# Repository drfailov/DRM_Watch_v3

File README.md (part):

<!-- For new line: \ -->
<!-- Picture:   -->
<!-- New Line: "  <br>"  -->

# Про проект DRM Watch 3

**DRM Watch 3** - це мій саморобний наручний годинник, в основі якого лежить дисплей Sharp Memory LCD, ESP32-S2 і бажання носити це на руці:)  <br>
Це **НЕ "Smart годинник"**! Цей пристрій по своїй функціональності близький до звичайного електронного годинника, з кількома додатковими можливостями, і їх можна додавати, перепрограмовувати годинник під себе.  <br>
Наразі в прошивці є всі можливості, що притаманні типовому годиннику і що дозволяє повноцінно використовувати його на щоденній основі.  <br>
В цьому репозиторії можна знайти інфу і інструкції **щоб зібрати собі такий годинник**.  <br>
  <br>
Це у мене таке хобі:) Я в кінці 2023 поліз вивчати проектування плат, після появи 3д принтера в 2022 поліз вивчати 3д моделювання, а за освітою програміст.  От власне це все і зібралось воєдино в цьому проекті) Робив це все з нуля. А яка б класна з цього була дипломна робота)))  <br>
  <br>
Посилання що наведено в цьому тексті є актуальними станом на **2024-04**. Якщо якісь товари будуть вже не актуальні, то шукайте за фотками))  <br>
  <br>
Стаття на Instructables:  <br>
https://www.instructables.com/DIY-ESP32-Wearable-DRM-Watch-3/    <br>
	  <br>

## Фото
<!--p align="center">

</p-->

<!--p align="center">

</p-->

## Особливості годинника
- Зроблено в Україні;
- Стабільно працює і підходить для щоденного користування;
- Дисплей завжди показує час;
- Інтерфейс двома мовами: Українська та Англійська.
- В годиннику є вбудована "флешка" на 1.2МБ, в яку можна закинути файли
- Годинник може відкрити монохромний BMP, Wav файли, текстовий TXT документи
- Є дуже тускла але дуже приємна нічна підсвітка дисплея;
- Є ліхтарик, білий яскравий та червоний нічний;
- Акумулятора вистачає на понад 14днів, є індикатор заряду;
- Зручні меню, звідки можна отримати доступ до всіх функцій;
- Наявність Wi-Fi, можна зберегти до 8 мереж в пам'яті;
- Можливість синхронізації часу по Wi-Fi;
- Багато мелодій. Їх можна або просто слухати або встановити на будильник.
- Імітація звуку мявчання кошенят;
- Кілька циферблатів, які можна налаштувати;
- На циферблати можна додати календар, стрілочний годинник, дату, та цікавий фон
- Секундомір, працює в фоні;
- Будильники, до 6шт з назвами;
- Вічний календар (або я ще не догортав до кінця);
- Повнекранні клітинні автомати та анімації (Життя, Мураха, Вогонь, Шум, Лава, Мураха, Точки)
- Зарядка по USB, в тому числі від TypeC-TypeC;
- Можна оновлювати прошивку по USB, не розбираючи годинник.
- Компоненти для збірки легко дістати;
- Корпус підходить для стандартних 22мм ремінців;
- Зручно і просто прошивати. Можна написати свою прошивку.
- Якщо під час експериментів з прошивками годинник завис, в корпусі передбачено отвір щоб голкою його перезавантажити.
- Водонепроникність до 0 метрів:) (можна трохи покращити якщо при збірці обробити плату лаком а корпус збирати з клеєм.)
- Годинник можна використовувати як поле для експериментів з ESP32-S2: акумулятор, 3 кнопки, пищалка, дисплей, 3 світлодіоди;
- UART лог: інструмент для розробників, виводить на екран всі байти що надходять по UART.
- Екран "Про годинник" містить інформацію про розробника та версію прошивки.

## Застереження під час користування:

- Годинник **не можна мочити**. Захист від води тут майже відсутній і це призведе до поломки годинника. Від дрібного дощу або поту йому нічого не буде, а от залити при митті рук - може бути проблемою.
- Годинник **слабко захищений від ударів**. Дисплей не захищений, тонкі рамки, тонкий корпус, годинник спроектований без великого запасу механічної міцності, так він  ще й досить габаритний. Тому вдарити його легко, і це скоріше за все призведе до розбитого дисплея. Протягом моїх місяців експлуатації проблем з пошкодженням годинника не було, але я користувався досить обережно.
- Годинник варто **оберігати від впливу статики**. Є невеликий шанс вбити годинник якщо швидко змімати з себе светр) Тому або знімайте светр повільно, або зніміть перед цим годинник, або використовуйте светр який не електризується. Особливо ризикований момент - постановка на зарядку, тут може проскочити прямо через контроллер. Раджу перед тим як вставити кабель зарядки, доторкнутись до металевої частини корпусу зарядного пристрою - так ви розрядитесь через корпус, а не через годинник і все буде ок.

## Відео огляди годинника:
Тут я зібрав наявні відео годинника.

### Короткий огляд станом на FW v2.03
  <br>
https://www.youtube.com/watch?v=3oIwZVaCEvY

### Повний огляд годинника станом на FW v3.22
  <br>
https://youtu.be/EeJpstsf5wk?si=9BsKVnumjvJCgt0X

## Короткий відео огляд мелодій станом на FW v2.03
  <br>
https://www.youtube.com/watch?v=Ylm3CU0DTDE

### Мій акаунт тікток, де відео багато
  <br>
https://www.tiktok.com/@drfailov

# Опис меню, функцій та екранів

## Основний екран, циферблат
<p align="center"> 

<!--img src="Photos/photo_2_2024-06-02_22-49-14.jpg" height=200"/> 

</p>

Тут відображаєтья час. Це основний екран годинника, на нього переходят більшість екранів по таймеру бездіяльності. На цьому екрані годинник заходить в сон і спить, просинаючись раз в хвилину щоб намалювати час.     <br>
Вміст циферблату можна налаштувати під себе, тому тут так багато різних його фоток        <br>
**Кнопка вгору** (коротке натиснення) - Відкрити секундомір.      <br>
**Кнопка вгору** (довге натиснення) - Відкрити таймер.      <br>
**Середня кнопка** (коротке натиснення) - Увімкнути ліхтарик.      <br>
**Середня кнопка** (довге натиснення) - вимкнути годинник.      <br>
**Кнопка вниз** - відкрити меню програм.      <br>

## Програми

<p align="center"> 
 
<!--img src="Photos/photo_3_2024-06-02_22-49-14.jpg" height=300"/--> 
</p>

Звідси можна запустити функції які не є налаштуваннями. Будильники, секундоміри, ігри, розваги, тощо.     <br>
З цього екрану годинник автоматично перейде на основний екран через кілька хвилин бездіяльності.    <br>
**Кнопками вгору та вниз** - обрати пункт меню.     <br>
**Центральна кнопка** - активує обраний пункт меню.      <br>

## Програми -> Будильник

Будильник запускає відтворення заданої мелодії в заданий час дня.     <br>
З цього екрану годинник автоматично перейде на основний екран через кілька хвилин бездіяльності.    <br>
Можна налаштувати кілька будильників. До кожного можна задати час, назву та мелодію. Будильник спрацює якщо годинник заряджений і якщо годинник звісно знає поточний час. Спрацює також якщо в момент спрацювання ви знаходитесь в меню а не на циферблаті, а також спрацює якщо годинник вимкнено (але він при цьому заряджений).     <br>
**Кнопками вгору та вниз** - обрати пункт меню.      <br>
**Центральна кнопка** активує обраний пункт меню.      <br>
Коли пункт меню активований, **кнопки вниз та вгору міняють значення пункту**.     <br>
Під час будильника гратиме обрана мелодія і відображатиметься назва будильника та час на який будильник було встановлено. Під час спрацювання будильника його можна закрити (вимкнути на поточний раз), або вікласти на 10 або 5 хвилин (за умови якщо в цей момент не запущено таймер). Після спрацювання будильника він спрацює знову наступного дня. 

## Програми -> Календар

<p align="center"> 
 
<!--img src="Photos/photo_14_2024-06-02_22-49-14.jpg" height=300"/--> 
</p>

Показує календар на місяць.     <br>
З цього екрану годинник автоматично перейде на основний екран через кілька хвилин бездіяльності.    <br>
**Кнопками вгору та вниз** - змінити поточний місяць.     <br>
**Центральна кнопка** - вийти.     <br>

## Налаштування

## Налаштування -> Дисплей

### Інверсія

### Мова

### Калібрування акумулятора 

Кожен годинник - унікальний, тому кожен показує заряд по своєму.      <br>
Щоб компенсувати цю неточність, я додав алгоритм який це виправляє, але для цього йому потрібно знати свою криву розряду. Щоб провести калібрування:      <br>
- повністю зарядити годинник 
- зняти з зарядки і пройти в налаштування -> дисплей ->калібрування акумулятора
- натиснути там початок калібровки.
- лишити годинник увімкненим на кілька годин поки він не вимкнеться.
Коли годинник вимкнеться, його можна поставити на зарядку і після цього він буде готовий до роботи з новою калібровкою     

## Програми -> Файли

Важливо!!! Не зберігайте на годиннику цінну інформацію яка не має копії! У мене кілька разів "ламалась" файлова система і файли втрачались. 
Закономірностей цього явища поки не виявив, але я б не довіряв годиннику нічого цінного!

Формати файлів які може відкрити годинник:
- BMP монохромний. Такі файли можна сформувати з допомогою Microsoft Paint.
- DWM мелодії. Такі файли можна сформувати з допомогою програми в папці `Software\MIDI-to-Arduino-main`.
- WAV PCM 8bit аудіо. Такі файли можна сформувати з допомогою Audacity.
- TXT текстові файли в UTF8 кодуванні. Такі файли можна сформувати з допомогою Notepad++.

## Програми -> Менеджер пам'яті

**Підключити до USB** - імітує підключену флешку.
**Показати карту розділів** - Відображає як поділена пам'ять ESP32.

## Програми -> Мелодії

Меню зі списком мелодій. Можна переглянути назви та увімкнути мелодію. Їх там багато.     <br>
Я постійно додаю нові мелодії, зокрема з мемів. Додати свої мелодії також можливо, дивіться розділ як зібрати прошивку а потім як додати мелодію.     <br>
З цього екрану годинник автоматично перейде на основний екран через кілька хвилин бездіяльності.    <br>
**Кнопками вгору та вниз** - обрати мелодію.     <br>
**Центральна кнопка** - відкрити і відтворити мелодію.   <br>

## Програми -> Мелодії -> Плеєр

Коли грає мелодія. Цей екран може бути запущений при спрацюванні будильника або якщо відкрити мелодію зі списку.    <br>
Якщо запущений при спрацюванні будильника:    <br>
**Кнопками вгору та вниз** - відкласти будильник. Мелодія зупиниться і буде запущено таймер на 10 або 5 хвилин. Якщо якийсь таймер вже запущений - відкласти будильник не вийде.     <br>
**Центральна кнопка** - Зупинити відтворення мелодії та повернутись до попереднього меню.      <br>  

Якщо запущений при відкриванні мелодії зі списку:    <br>
**Кнопка вниз** - увімкнути або вимкнути повтор мелодії. Якщо запущено повтор, в статусному рядку відображатиметься відповідна піктограма, а мелодія гратиме доки годинник не розрядиться.      <br>
**Центральна кнопка** - Зупинити відтворення мелодії та повернутись до попереднього меню.      <br> 

## Програми -> Таймер

Таймер веде відлік заданого часу від моменту запуску. Коли час спливає, запускається звуковий сигнал.      <br>
З цього екрану годинник автоматично перейде на основний екран через кілька хвилин бездіяльності.    <br>  
**Кнопками вгору та вниз** - задається час на який встановлюється таймер.    <br> 
**Центральна кнопка** - або закриває програму, або запускає таймер.     <br> 
Коли лунає звуковий сигнал, його можна закрити, або вікласти на 10 або 5 хвилин.

## Програми -> Секундомір

Веде відлік часу від моменту запуску.       <br> 
На цьому екрані годинник спить, і не виходить на циферблат.      <br> 
Секундомір може працювати в фоні. 
Поточне значення секундоміра (години, хвилини) відображатиметься в статусному рядку у всіх вікнах програми.       <br> 
Внизу відображається історія, які значення коли були скинуті.       <br> 
**Кнопка вгору** - Запустити або призупинити секундомір.     <br> 
**Кнопка вниз** - Скидає показник секундоміра.     <br> 
**Центральна кнопка** - вихід на циферблат.     <br> 

## Програми -> Ліхтарик

Запускає ліхтарик. Програма при цьому ніяка не відкривається, просто вмикається світло.      <br> 
У ліхтарика два режими роботи - червоним світлодіодом і білим.       <br> 
Червоний буде корисним вночі - так він не сліпить і після його використання буде все ще добре видно вночі. 
Денний ліхтарик більш яскравий.      <br> 
Ліхтарик автоматично вимкнеться через кілька хвилин бездіяльності.  <br> 
**Один раз натиснути на кнопку** - якщо ліхтарик вимкнено - увімкнути нічний ліхтарик.      <br> 
**Другий раз натиснути** - увімкнути денний режим.      <br> 
**Якщо ліхтарик вже світить** - більше 5 секунд, то натиснення на кнопку його вимкне.      <br> 
Тобто якщо вночі запустити нічний ліхтарик, покористуватись ним, то натиснення на іконку ліхтарика не запустить денний ліхтар а вимкне ліхтар.      <br> 
Щоб запустити денний ліхтар - кнопку треба натиснути двічі протягом 2 секунд.      <br> 

## Програми -> Інженерне меню

На цьому екрані зібрано максимум технічної інформації яка допоможе зрозуміти стан системи.      <br> 
На цьому екрані годинник спить, і не виходить на циферблат.      <br> 
**Центральна кнопка** - вийти до меню програм.      <br> 
**Кнопка вгору** - активувати чи вимкнути режим безсоння     <br>
В режимі безсоння годинник не буде йти в сон по таймеру. 
В цьому режимі годинник дуже швидко розрядиться, за кілька годин. 
В режимі безсоння в статусбарі буде відображатись інонка з кавою, а в інженерному меню буде написано "Don't sleep: 1".     <br>

## Програми -> Лог UART

Годинник при підключенні до компа імітує на компі **COM порт**. 
Всі дані що надходять на COM порт - виводяться в лог на екрані.   <br>
Це може бути корисно якщо потрібно зрозуміти яку команду надсилає 
невідома вам програма до підключеного пристрою в процесі, наприклад, діагостики або реверс інжинірінгу.   <br>
Відображення відбувається в форматі лога, можна виводити як в текстовому форматі (ASCII) так і в форматі шістнадцяткових байтів (HEX).  <br>
На цьому екрані годинник не спить і не виходить на циферблат автоматично! Він буде увімкнений доти, доки його не вимкнути вручну або він не розрядиться повністю.  <br>
**Кнопка вгору** - ставить зображення на паузу - якщо потрібно детальніше вивчити отримані дані. Нові дані не будуть виводитись на екран.  <br>
**Центральна кнопка** - вийти до меню програм.  <br>
**Кнопка вниз** - перемкнути режим відображення (ASCII чи HEX).  <br>

## Програми -> Meow

Симуляція мявчання кошенят. Генерується програмно випадковим чином. Можна обрати тон мявчання та вийти.

## Програми -> Життя

Режим повноекранного кліткового автомату "Життя" (Convey's Game Of Life).    <br>
**Будь-яка з кнопок** - повернутись до меню програм.    <br>

## Програми -> Вогонь

Режим повноекранної анімації вогню. Красиво. В основі лежить шум Перліна.    <br>
**Будь-яка з кнопок** - повернутись до меню програм.    <br>
Дякую за допомогу з реалізацією Кирилу Лейферу, ось його репозиторій: https://github.com/BOOtak/dct3ngine/blob/master/src/games/perlin_test

## Програми -> Лава

Режим повноекранної анімації лави. Красиво. В основі лежить шум Перліна.    <br>
**Будь-яка з кнопок** - повернутись до меню програм.    <br>
Дякую за допомогу з реалізацією Кирилу Лейферу, ось його репозиторій: https://github.com/BOOtak/dct3ngine/blob/master/src/games/perlin_test

## Програми -> Мураха

Режим повноекранного кліткового автомату "Мураха Ленгтона".    <br>
**Кнопки вниз або вгору** - змінити швидкість симуляції.    <br>
**Середня кнопка** - повернутись до меню заставок.    <br>

## Налаштування -> Вміст циферблату
Одночасно відображатиметься тільки один фон, тому щоб був відображався потрібний фон, потрібно залишити активний тільки один з доступних.    <br>
Кнопками вгору та вниз - обрати пункт меню. Центральна кнопка міняє обраний пункт меню. 

# Як зібрати годинник
Готових годинників в продажу не існує, тому якщо є бажання отримати такий годинник, можна зібрати самому.  <br>  

## Що знадобиться

- Паяльник
- Припой
- Паяльний фен або столик
- Флюс
- Пінцети
- Викрутки
- Мікроскоп (бажано)

## Де брати комплектуючі

Якщо коротко, то:  <br>  
- Board: Order PCB on jlcpcb, GERBER included  <br>  
- Front panel: order alluminium CNC Milling on jlcpcb, STEP included  <br>  
- Back panel: 3d print, STL included  <br>  
- Display Sharp LS027B7DH01A  <br>  
https://www.aliexpress.us/item/1005005611440829.html  <br>  
- Connector FPC 10pin 0.5mm pitch  <br>  
https://www.aliexpress.us/item/10000348360254.html  <br>  
- Battery lipo 502535  <br>  
https://ampul.eu/de/batterie/4242-li-pol-akku-450mah-37v-502535  <br>  
- Buzzer SMD 7525-3.6V-passive  <br>  
https://www.aliexpress.us/item/1005003620083880.html  <br>  
- Mosfet 2N7002LT1G  <br>  
https://www.aliexpress.us/item/1005003079655220.html  <br>  
- Esp32 board: Lolin S2 Mini  <br>  
https://www.aliexpress.us/item/1005004438665554.html  <br>  
- TP4056 Charging module  <br>  
https://www.aliexpress.com/item/1005006310424899.html  <br>  
- Resistor set SMD 0603  <br>  
https://www.aliexpress.us/item/1005002364437129.html  <br>  
- Capacitors set SMD 0603  <br>  
https://www.aliexpress.us/item/1005006124283234.html  <br>  
- RTC Module based on Analog Devices DS3231   <br>  
https://www.aliexpress.us/item/32822420722.html  <br>  
- 020 SMD Side View LED White 6000K  <br>  
https://www.aliexpress.us/item/32419907074.html  <br>  
- Buttons 2\*4\*3.5mm Micro SMD Tact Switch Side Button  <br>  
https://www.aliexpress.us/item/1005004312046546.html  <br>  
- Screw places SMTSO Surface Mount Copper Nut M1.4X3X1.5-2X0.8  <br>  
https://www.aliexpress.com/item/1005005579653583.html  <br>  
- Screws PH000, M1.4, 3mm length  <br>  
https://www.aliexpress.com/item/1005002364568213.html  <br>  
- Self tapping screws M1.5, 6mm  <br>  
https://www.aliexpress.com/item/1005002324715062.html  <br>  
- Watch band, 22мм   <br>  
https://www.aliexpress.us/item/1005005890436737.html  <br>  
- USB Type C cover:  <br>  
https://www.aliexpress.com/item/4000148621089.html  <br>  
- EL Panel driver: Microchip HV857MG MSOP8  (optional, only if you want backlight)  <br>  
https://www.aliexpress.us/item/1005005512523052.html  <br>  
- EL Driver Capacitor SMD 1206 10NF X7R 200V (optional, only if you want backlight)  <br>  
https://www.aliexpress.us/item/1005004628006766.html  <br>  
- EL Driver Capacitors SMD 1206 320PCS 16Value   (optional, only if you want backlight)  <br>  
https://www.aliexpress.us/item/1005006124283234.html   <br>  
- EL Driver Diode ES1D   (optional, only if you want backlight)  <br>  
https://www.aliexpress.us/item/1005005254835443.html  <br>  
- EL Driver  SMD Inductor 1210 3225 22UH   (optional, only if you want backlight)  <br>  
https://www.aliexpress.us/item/32981310345.html  <br>  
- Glue to connect EL panel MECHANIC MCN-DJ002 Conductive Adhesive Glue Silver (optional, only if you want backlight)  <br>  
https://www.aliexpress.us/item/1005002369819447.html  <br>  

### Дисплей

Дисплей потрібен, щоб відображати інформацію користувачу:)  <br>
Модель дисплея: **Sharp LS027B7DH01A**    <br>
Він звісно недешений, але мені дуже подобається як він виглядає. Його можна купити готовим, я купував тут:   <br>
https://www.aliexpress.us/item/1005005611440829.html  <br>

### Конектор дисплея

Для підключення цього дисплея. Я купував модулем, але можна пошукати і роз'єм окремо.  <br>
Модель: **FPC 10pin 0.5mm pitch** Я купував тут:    <br>
https://www.aliexpress.us/item/1005002288363000.html   <br>
https://www.aliexpress.us/item/10000348360254.html   <br>

### Акумулятор

Якщо потрібно щоб пристрій працював автономно, то потрібен акумулятор.  <br>
Корпус та плата спроектовано під літій-іонний акумулятор такої форми: 35*25*5mm. Звісно, підійде будь-який і меншого розміру, але матиме меншу ємність.  <br>
Модель яка найкраще підходить: **lipo 502535**. Я купував тут:    <br>
https://prom.ua/ua/p1286391849-akkumulyator-kontrollerom-universalnyj.html   <br>
https://ampul.eu/de/batterie/4242-li-pol-akku-450mah-37v-502535   <br>

### Буззер

Буззер потрібен щоб пищати, грати мелодії.  <br>
Модель: **Buzzer SMD 7525-3.6V-passive**. Я купував тут:    <br>
https://www.aliexpress.us/item/1005003620083880.html   <br>
https://eu.mouser.com/ProductDetail/CUI-Devices/CMT-7525S-SMT-TR?qs=qCxwlXJ4fnw4ZHFvNib47A%3D%3D

### Мосфет

Мосфет використовується для того щоб керувати буззером, щоб на нього надходив не слабкий сигнал з мікроконтроллера, 
а потужний з батареї.    <br>
Модель: **2N7002LT1G**. Можна купити тут:    <br>
https://www.aliexpress.us/item/1005003079655220.html    <br>

### ESP32

Я розпаював на комплектуючі плати **Lolin S2 Mini**, ось ссилка де я купував:  <br>
https://www.aliexpress.us/item/1005004438665554.html  <br>
  <br>
Якщо немає бажання розпаювати Lolin S2 Mini, можна купити комплектуху окремо:  <br>

Датащіт:
https://www.espressif.com/sites/default/files/documentation/esp32-s2_datasheet_en.pdf 
Чіп: **ESP32-S2FN4R2, QFN56**  <br>
https://www.tme.eu/ua/details/esp32s2fn4r2/moduli-iot-wifi-bluetooth/espressif/esp32-s2fn4r2   <br>
Кварц: **SMD 3225 4pin 40MHz**:  <br>
https://www.aliexpress.us/item/1005004689346275.html  <br>

### Модуль зарядки акумулятора

Щоб була можливість заряджати акумулятор. Причому якщо акума не буде - годинник не працюватиме навіть на зарядці.   <br>
https://www.aliexpress.com/item/1005006310424899.html
Тому якщо потрібно обійти модуль зарядки, можна замкнути перемичку біля мікросхеми заряду на платі (вона вона розташована біля самого краю плати) - вона подасть напряму напругу з USB порта замість напруги батареї. Основне не залишити перемичку зі вставленим акумом, щоб не отримати **фаєр-шоу**)))   <br>
Розпаявши такий модуль можна дістати чіп **TP4056** , який відоповідає за зарядку акума. Датащит:  <br>
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
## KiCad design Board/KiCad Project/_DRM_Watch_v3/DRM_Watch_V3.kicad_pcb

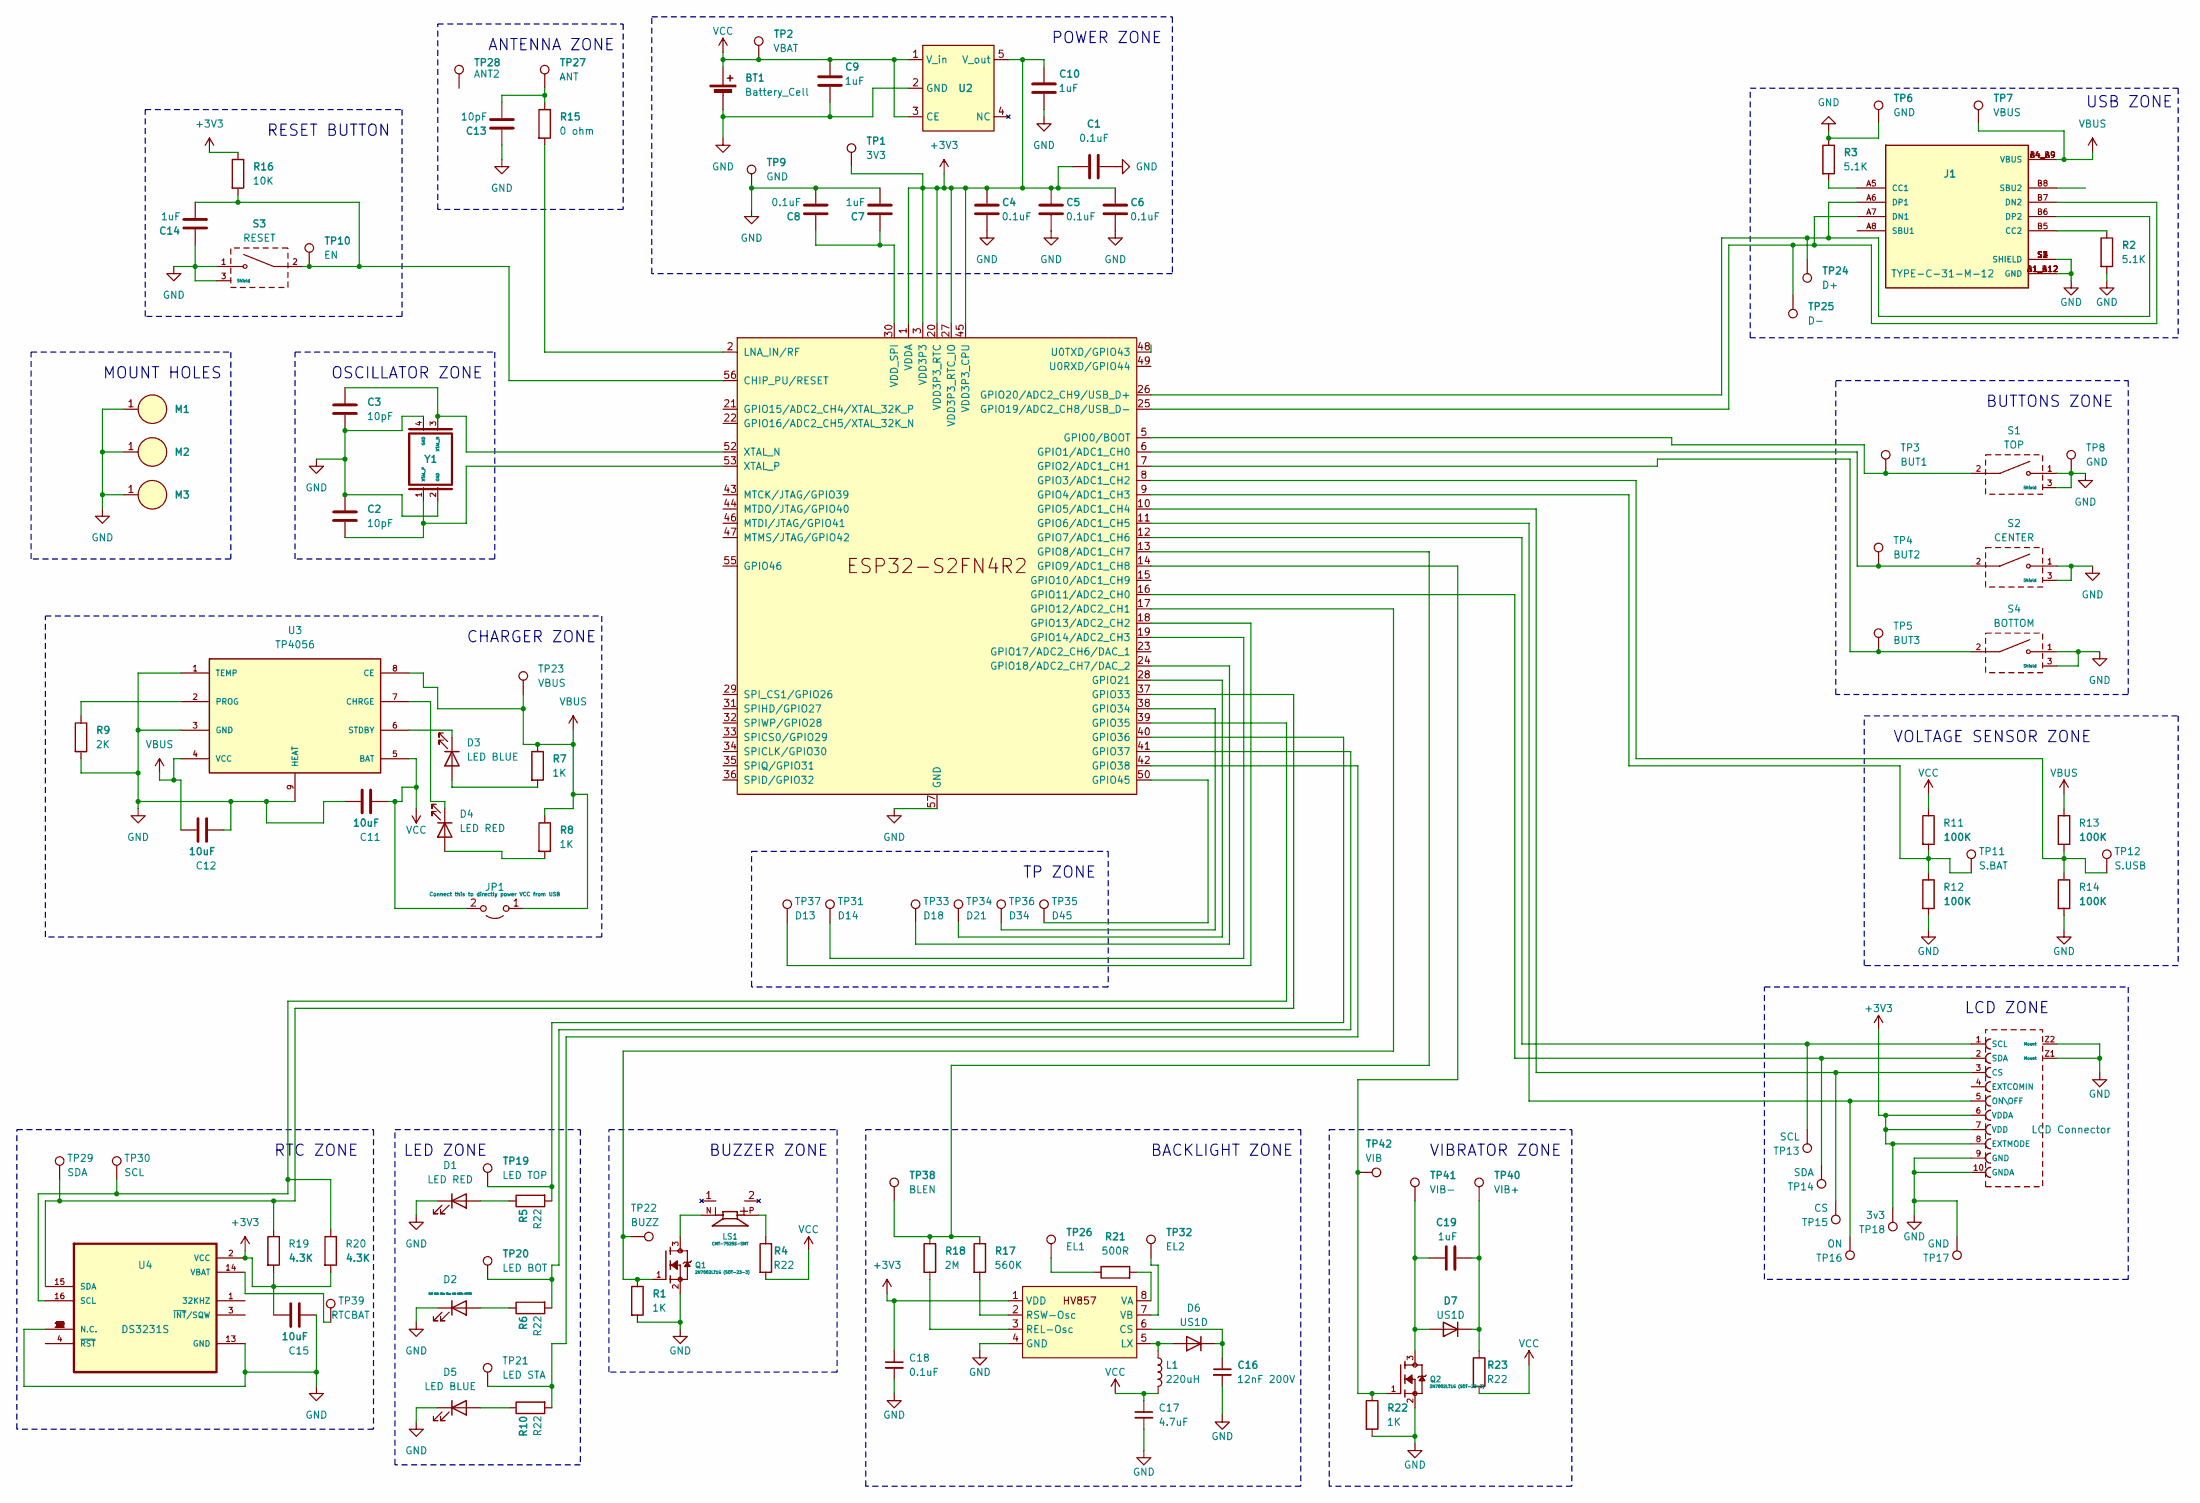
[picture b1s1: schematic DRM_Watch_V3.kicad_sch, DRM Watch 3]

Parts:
BT1: Battery_Cell; Battery
C1: 0.1uF; C_0805_2012Metric
C2, C3, C13: 10pF; C_0603_1608Metric
C4, C5, C6, C8: 0.1uF; C_0603_1608Metric
C7, C14: 1uF; C_0603_1608Metric
C9, C10, C19: 1uF; C_0805_2012Metric
C11, C12, C15: 10uF; C_0603_1608Metric
C16: 12nF 200V; C_1206
C17: 4.7uF; C_1206
C18: 0.1uF; C_1206
D1, D4: LED RED; HOLE_LED_0805_2012Metric
D2: 020 SMD Side View LED White 6000K; SMD-LED-Side-View
D3, D5: LED BLUE; HOLE_LED_0805_2012Metric
D6, D7: US1D
J1: TYPE-C-31-M-12; HRO_TYPE-C-31-M-12
J2: FPC 10pin 0.5mm pitch; 687110149022
JP1: Connect this to directly power VCC from USB; SolderJumper-2_P1.3mm_Open_Pad1.0x1.5mm
L1: 220uH; Inductor-L_1210_3225Metric
LS1: CMT-7525S-SMT; CUI_CMT-7525S-SMT
M1, M2, M3: Brass SMTSO-M1.4X3X1.5-2X0.8; m1.4-screw-mount
Q1, Q2: 2N7002LT1G (SOT-23-3); SOT95P240X111-3N
R1, R7, R8, R22: 1K; R_0603_1608Metric
R2, R3: 5.1K; R_0603_1608Metric
R4, R5, R6, R10, R23: R22; R_0603_1608Metric
R9: 2K; R_0603_1608Metric
R11, R12, R13, R14: 100K; R_0603_1608Metric
R15: 0 ohm; R_0603_1608Metric
R16: 10K; R_0603_1608Metric
R17: 560K; R_0603_1608Metric
R18: 2M; R_0603_1608Metric
R19, R20: 4.3K; R_0603_1608Metric
R21: 500R; R_0603_1608Metric
S1, S2, S3, S4: 2*4*3.5mm Micro SMD Tact Switch Side Button; SW_TL3330AF130QG
TP1: 3V3; TestPoint_Pad
TP2: VBAT; TestPoint_Pad
TP3: BUT1; TestPoint_Pad
TP4: BUT2; TestPoint_Pad
TP5: BUT3; TestPoint_Pad
TP6, TP8, TP9, TP17: GND; TestPoint_Pad
TP7, TP23: VBUS; TestPoint_Pad
TP10: EN; TestPoint_Pad
TP11: S.BAT; TestPoint_Pad
TP12: S.USB; TestPoint_Pad
TP13, TP30: SCL; TestPoint_Pad
TP14, TP29: SDA; TestPoint_Pad
TP15: CS; TestPoint_Pad
TP16: ON; TestPoint_Pad
TP18: 3v3; TestPoint_Pad
TP19: LED TOP; TestPoint_Pad
TP20: LED BOT; TestPoint_Pad
TP21: LED STA; TestPoint_Pad
TP22: BUZZ; TestPoint_Pad
TP24: D+; TestPoint_Pad
TP25: D-; TestPoint_Pad
TP26: EL1; TestPoint_Pad
TP27: ANT; TestPoint_Pad
TP28: ANT2; TestPoint_Pad
TP31: D14; TestPoint_Pad
TP32: EL2; TestPoint_Pad
TP33: D18; TestPoint_Pad
TP34: D21; TestPoint_Pad
TP35: D45; TestPoint_Pad
TP36: D34; TestPoint_Pad
TP37: D13; TestPoint_Pad
TP38: BLEN; TestPoint_Pad
TP39: RTCBAT; TestPoint_Pad
TP40: VIB+; TestPoint_Pad
TP41: VIB-; TestPoint_Pad
TP42: VIB; TestPoint_Pad
U1: ESP32-S2FN4R2; QFN-56-1EP_7x7mm_P0.4mm_EP4x4mm_ThermalVias
U2: ME6211 SOT23-5 3.3V; ME6211 SOT-23-5
U3: TP4056; SO08
U4: DS3231S; SOIC127P1032X265-16N
U5: Microchip HV857; HV857
Y1: 3225 4PIN 40Mhz 3.2*2.5mm Passive SMD Quartz Reso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; Oscilator

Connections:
+3V3: C1.2, C4.1, C5.1, C6.1, C10.1, C15.2, C18.1, J2.6 (VDDA), J2.7 (VDD), J2.8 (EXTMODE), R16.1, R19.2, R20.2, TP1.1, TP18.1, U1.1 (VDDA), U1.3 (VDD3P3), U1.4 (VDD3P3), U1.20 (VDD3P3_RTC), U1.27 (VDD3P3_RTC_IO), U1.45 (VDD3P3_CPU), U1.51 (VDDA), U1.54 (VDDA), U2.5 (V_out), U4.2 (VCC), U5.1 (VDD)
GND: BT1.2 (-), C1.1, C2.1, C3.2, C4.2, C5.2, C6.2, C7.2, C8.2, C9.2, C10.2, C11.2, C12.1, C13.1, C14.1, C15.1, C16.2, C17.2, C18.2, D1.1 (K), D2.1 (K), D5.1 (K), J1.A1_B12 (GND), J1.B1_A12 (GND), J1.S1 (SHIELD), J1.S2 (SHIELD), J1.S3 (SHIELD), J1.S4 (SHIELD), J2.9 (GND), J2.10 (GNDA), J2.Z1 (Mount), J2.Z2 (Mount), M1.1, M2.1, M3.1, Q1.2, Q2.2, R1.2, R2.2, R3.1, R9.2, R12.2, R14.2, R22.2, S1.1, S1.3 (Shield), S2.1, S2.3 (Shield), S3.1, S3.3 (Shield), S4.1, S4.3 (Shield), TP6.1, TP8.1, TP9.1, TP17.1, U1.57 (GND), U2.2 (GND), U3.1 (TEMP), U3.3 (GND), U3.9 (HEAT), U4.5 (N.C.), U4.6 (N.C.), U4.7 (N.C.), U4.8 (N.C.), U4.9 (N.C.), U4.10 (N.C.), U4.11 (N.C.), U4.12 (N.C.), U4.13 (GND), U5.4 (GND), Y1.2 (GND), Y1.4 (GND)
unnamed: C13.2, R15.1, TP27.1
unnamed: D1.2 (A), R5.1
unnamed: D2.2 (A), R6.1
unnamed: D3.2 (A), R7.2
unnamed: D3.1 (K), U3.6 (STDBY)
unnamed: D4.2 (A), R8.2
unnamed: D4.1 (K), U3.7 (CHRGE)
unnamed: D5.2 (A), R10.1
unnamed: D6.2 (A), L1.1, U5.5 (LX)
unnamed: C16.1, D6.1 (K), U5.6 (CS)
unnamed: C19.1, D7.2 (A), Q2.3, TP41.1
unnamed: C19.2, D7.1 (K), R23.1, TP40.1
unnamed: J1.A5 (CC1), R3.2
unnamed: J1.B5 (CC2), R2.1
unnamed: J1.A7 (DN1), J1.B7 (DN2), TP25.1, U1.25 (GPIO19/ADC2_CH8/USB_D-)
unnamed: J1.A6 (DP1), J1.B6 (DP2), TP24.1, U1.26 (GPIO20/ADC2_CH9/USB_D+)
unnamed: J2.3 (CS), TP15.1, U1.10 (GPIO5/ADC1_CH4)
unnamed: J2.5 (ON\OFF), TP16.1, U1.11 (GPIO6/ADC1_CH5)
unnamed: J2.1 (SCL), TP13.1, U1.12 (GPIO7/ADC1_CH6)
unnamed: J2.2 (SDA), TP14.1, U1.16 (GPIO11/ADC2_CH0)
unnamed: LS1.N, Q1.3
unnamed: LS1.P, R4.1
unnamed: R21.1, TP26.1
unnamed: C14.2, R16.2, S3.2, TP10.1, U1.56 (CHIP_PU/RESET)
unnamed: S1.2, TP3.1, U1.5 (GPIO0/BOOT)
unnamed: S2.2, TP4.1, U1.6 (GPIO1/ADC1_CH0)
unnamed: S4.2, TP5.1, U1.7 (GPIO2/ADC1_CH1)
unnamed: R13.2, R14.1, TP12.1, U1.8 (GPIO3/ADC1_CH2)
unnamed: R11.2, R12.1, TP11.1, U1.9 (GPIO4/ADC1_CH3)
unnamed: R17.1, R18.1, TP38.1, U1.13 (GPIO8/ADC1_CH7)
unnamed: Q2.1, R22.1, TP42.1, U1.14 (GPIO9/ADC1_CH8)
unnamed: Q1.1, R1.1, TP22.1, U1.17 (GPIO12/ADC2_CH1)
unnamed: TP37.1, U1.18 (GPIO13/ADC2_CH2)
unnamed: TP31.1, U1.19 (GPIO14/ADC2_CH3)
unnamed: TP33.1, U1.24 (GPIO18/ADC2_CH7/DAC_2)
unnamed: TP34.1, U1.28 (GPIO21)
unnamed: R19.1, TP29.1, U1.37 (GPIO33), U4.15 (SDA)
unnamed: TP36.1, U1.38 (GPIO34)
unnamed: R20.1, TP30.1, U1.39 (GPIO35), U4.16 (SCL)
unnamed: R5.2, TP19.1, U1.40 (GPIO36)
unnamed: R6.2, TP20.1, U1.41 (GPIO37)
unnamed: R10.2, TP21.1, U1.42 (GPIO38)
unnamed: TP35.1, U1.50 (GPIO45)
unnamed: R15.2, U1.2 (LNA_IN/RF)
unnamed: C7.1, C8.1, U1.30 (VDD_SPI)
unnamed: C3.1, U1.52 (XTAL_N), Y1.3 (XTAL_N)
unnamed: C2.2, U1.53 (XTAL_P), Y1.1 (XTAL_P)
unnamed: R9.1, U3.2 (PROG)
unnamed: TP39.1, U4.14 (VBAT)
unnamed: R18.2, U5.3 (REL-Osc)
unnamed: R17.2, U5.2 (RSW-Osc)
unnamed: R21.2, U5.8 (VA)
unnamed: TP32.1, U5.7 (VB)
VBUS: C12.2, J1.A4_B9 (VBUS), J1.B4_A9 (VBUS), JP1.1 (A), R7.1, R8.1, R13.1, TP7.1, TP23.1, U3.4 (VCC), U3.8 (CE)
VCC: BT1.1 (+), C9.1, C11.1, C17.1, JP1.2 (B), L1.2, R4.2, R11.1, R23.2, TP2.1, U2.1 (V_in), U2.3 (CE), U3.5 (BAT)

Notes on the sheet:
MOUNT HOLES
OSCILLATOR ZONE
BUZZER ZONE
CHARGER ZONE
TP ZONE
LED ZONE
RESET BUTTON
BUTTONS ZONE
VOLTAGE SENSOR ZONE
USB ZONE
ANTENNA ZONE
VIBRATOR ZONE
LCD ZONE
POWER ZONE
RTC ZONE
BACKLIGHT ZONE

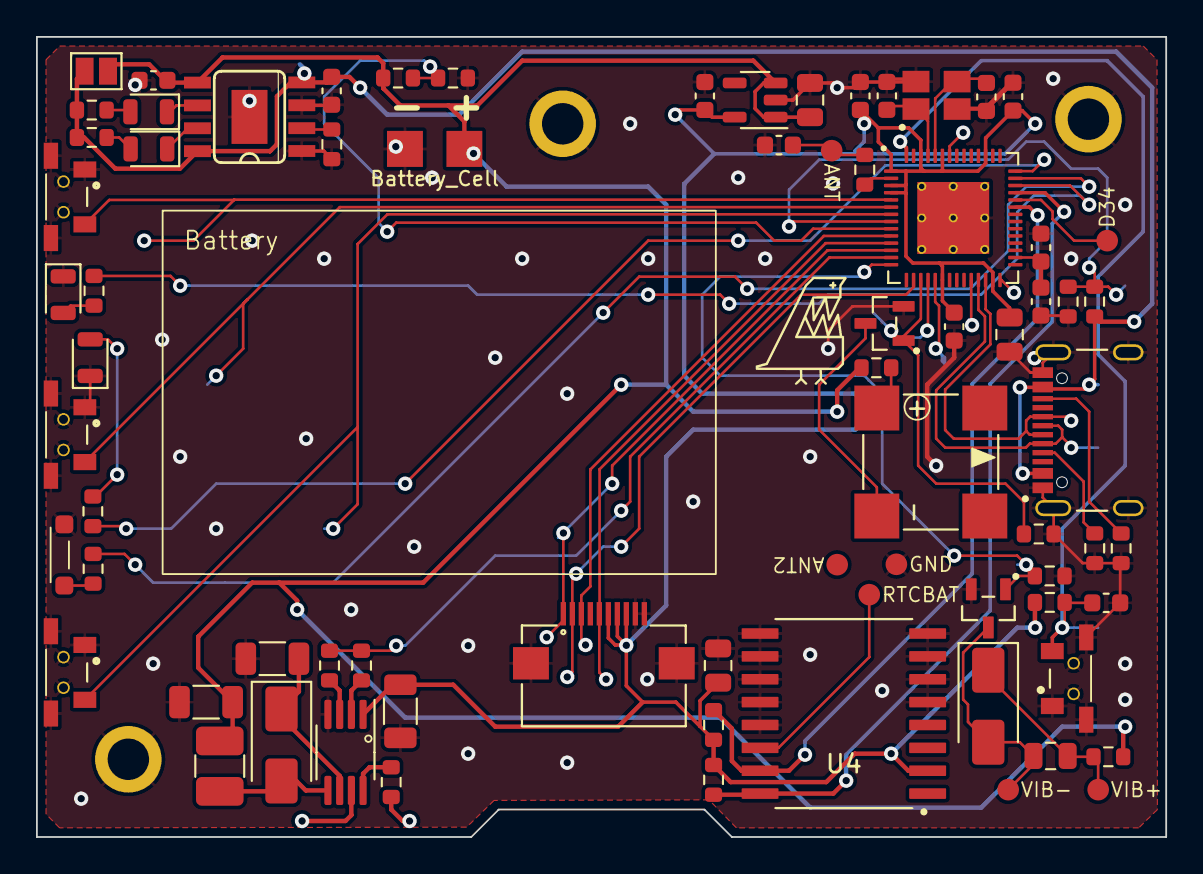
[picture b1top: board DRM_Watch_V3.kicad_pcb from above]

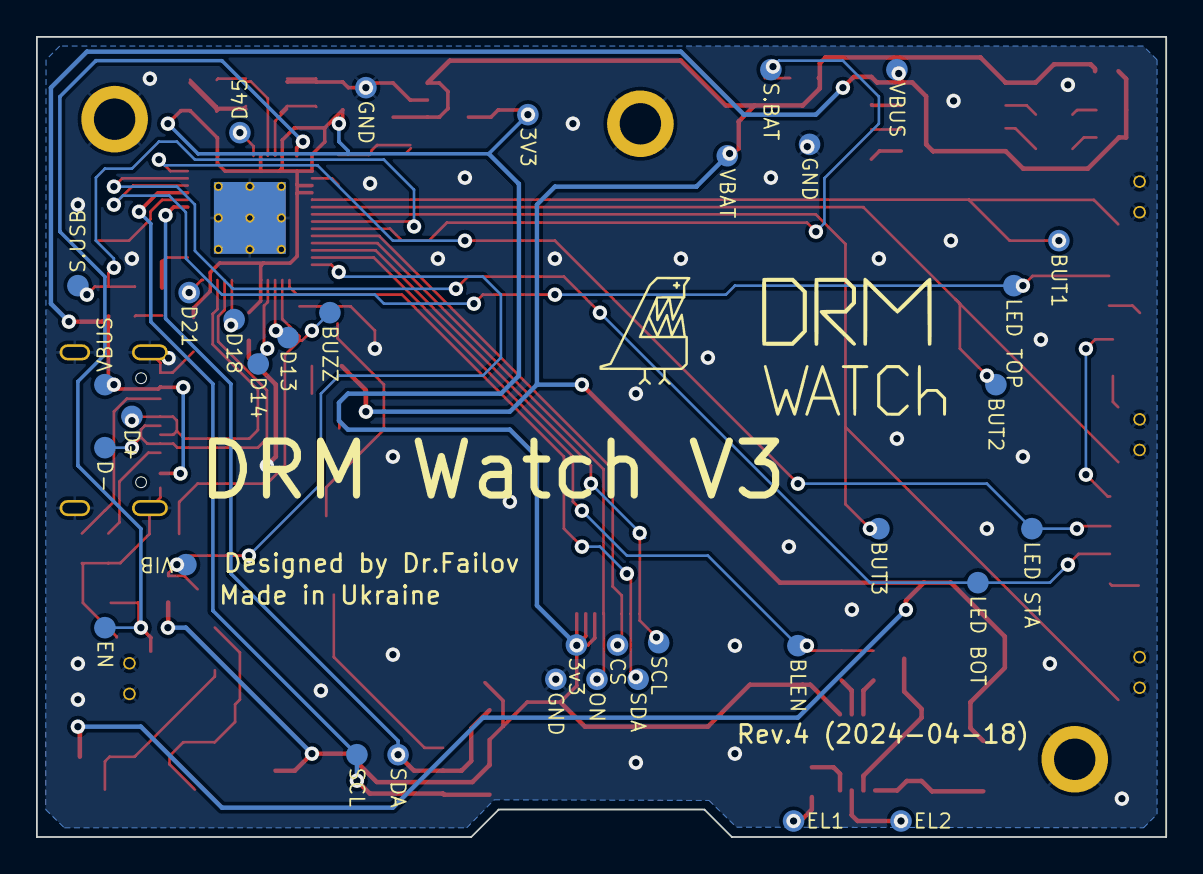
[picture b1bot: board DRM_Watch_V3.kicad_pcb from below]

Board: 2 copper layers, 62.7 x 44.4 mm, 112 parts (35 on the bottom side), 57 nets.

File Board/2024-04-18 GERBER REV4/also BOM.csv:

"Id";"Designator";"Footprint";"Quantity";"Designation";"Supplier and ref";
1;"R3,R2";"R_0603_1608Metric";2;"5.1K";;;
2;"D2";"SMD-LED-Side-View";1;"020 SMD Side View LED White 6000K";;;
3;"C18";"C_1206";1;"0.1uF";;;
4;"LS1";"CUI_CMT-7525S-SMT";1;"CMT-7525S-SMT";;;
5;"R14,R11,R13,R12";"R_0603_1608Metric";4;"100K";;;
6;"R6,R23,R10,R5,R4";"R_0603_1608Metric";5;"R22";;;
7;"M2,M3,M1";"m1.2-screw-mount";3;"M1.2 screw mount get from DJI Mavic 3 CORE board";;;
8;"C5,C6,C4,C8";"C_0603_1608Metric";4;"0.1uF";;;
9;"R19,R20";"R_0603_1608Metric";2;"4.3K";;;
10;"C15,C12,C11";"C_0603_1608Metric";3;"10uF";;;
11;"R9,R16";"R_0603_1608Metric";2;"10K";;;
12;"D3,D5";"HOLE_LED_0805_2012Metric";2;"LED BLUE";;;
13;"S2,S1,S4,S3";"SW_TL3330AF130QG";4;"2*4*3.5mm Micro SMD Tact Switch Side Button";;;
14;"C9,C19,C10";"C_0805_2012Metric";3;"1uF";;;
15;"Q1,Q2";"SOT95P240X111-3N";2;"2N7002LT1G (SOT-23-3)";;;
16;"R21";"R_0603_1608Metric";1;"500R";;;
17;"R17";"R_0603_1608Metric";1;"560K";;;
18;"U3";"SO08";1;"TP4056";;;
19;"D6,D7";"US1D";2;"US1D";;;
20;"J2";"687110149022";1;"FPC 10pin 0.5mm pitch";;;
21;"C7,C14";"C_0603_1608Metric";2;"1uF";;;
22;"C3,C13,C2";"C_0603_1608Metric";3;"10pF";;;
23;"R7,R22,R8,R1";"R_0603_1608Metric";4;"1K";;;
24;"U4";"SOIC127P1032X265-16N";1;"DS3231S";;;
25;"D1,D4";"HOLE_LED_0805_2012Metric";2;"LED RED";;;
26;"U5";"HV857";1;"Microchip HV857";;;
27;"R18";"R_0603_1608Metric";1;"2M";;;
28;"C16";"C_1206";1;"12nF 200V";;;
29;"U2";"ME6211 SOT-23-5";1;"ME6211 SOT23-5 3.3V";;;
30;"L1";"Inductor-L_1210_3225Metric";1;"220uH";;;
31;"C17";"C_1206";1;"4.7uF";;;
32;"R15";"R_0603_1608Metric";1;"0 ohm";;;
33;"J1";"HRO_TYPE-C-31-M-12";1;"TYPE-C-31-M-12";;;
34;"Y1";"OSC_XRCGB48M000F0Z00R0";1;"3225 4PIN 40Mhz 3.2*2.5mm Passive SMD Quartz Resonator Crystal";;;
35;"REF**";"Battery502535";1;"Battery502535";;;
36;"U1";"QFN-56-1EP_7x7mm_P0.4mm_EP4x4mm_ThermalVias";1;"ESP32-S2";;;
37;"C1";"C_0805_2012Metric";1;"0.1uF";;;

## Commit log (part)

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2023-12-27 Added files for tracking
2023-12-31 2023-12-31 v0.1 Started development of Keyboard
2024-01-01 2024-01-01 v0.1 New Question Window
2024-01-02 2024-01-01 v0.1 Significantly optimized connection to known network
2024-01-04 2024-01-04 v0.12 Melody Player 2024-01-04 v0.12 Vector Graphics 2024-01-04 v0.12 UI Improvement 2024-01-04 v0.12 Init screen
2024-01-09 2024-01-09 v0.16 auto-sync daily
2024-01-23 2024-01-24 Added instrument to convert MIDI files to melodies 2024-01-24 v0.19 New melodies
2024-01-31 2024-01-31 v0.22 Added meow function
2024-02-12 2024-02-12 v0.26 added support for DS3231M RTC Chip
2024-02-17 2024-02-15 v0.29 game of life working 2024-02-15 v0.29 when battey is low, modes with disabled auto-return will be forced to return
2024-02-20 2024-02-20 v0.31 calendar added and working
2024-02-27 2024-02-27 Board: Destroyed all the board wiring and start over.
2024-03-04 2024-03-04 v0.34 Fixed: Stopwatch screen is constantly returnng to watchface 2024-03-04 v0.34 Internal and external RTC now using UTC time and offset is added before use
    2024-03-04 v0.34 Fixed: Stopwatch screen is constantly returnng to watchface
    2024-03-04 v0.34 Internal and external RTC now using UTC time and offset is added before use
2024-03-13 2024-03-13 v0.37 Fixed animation 2024-03-13 v0.37 Додати анімацію тексту
    2024-03-13 v0.37 Fixed animation
    2024-03-13 v0.37 Додати анімацію тексту
2024-03-21 2024-03-21 v1.41 Зроблено: Затухати ліхтарик перед вимкненням 2024-03-21 v1.41 Оновлено дизайн Life циферблата 2024-03-21 v1.41 Зроблено: add dji logo 2024-03-21 v1.41 Виправлено: Іноді яскравість лі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
    2024-03-21 v1.41 Зроблено: Затухати ліхтарик перед вимкненням
    2024-03-21 v1.41 Оновлено дизайн Life циферблата
    2024-03-21 v1.41 Зроблено: add dji logo
    2024-03-21 v1.41 Виправлено: Іноді яскравість ліхтаря не доходить
2024-03-26 2024-03-26 v1.44 Анімація перед ребутом 2024-03-26 v1.44 Послідовність мелодій відсортована за алфавітом 2024-03-26 v1.44 Перейменовано: Carol of the bells - Щедрик 2024-03-26 v1.44 Виправлено цетрув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
2024-03-28 Added updated library
2024-04-07 2024-04-07 Доповнено документацію 2024-04-07 v2.04 Додано ще один варіант звуку кнопок 2024-04-07 v2.04 Виправлено: перший запуск - беззвучні кнопки
    2024-04-07 Доповнено документацію
    2024-04-07 v2.04 Додано ще один варіант звуку кнопок
    2024-04-07 v2.04 Виправлено: перший запуск - беззвучні кнопки
2024-04-07 2024-04-07 v2.04 Малювання питання, та повідомлення зі скругленими кутами
    2024-04-07 v2.04 Малювання питання, та повідомлення зі скругленими кутами
2024-04-08 2024-04-08 v2.05 Наче зробив імена будильникам 2024-04-08 v2.05 не виходити якщо пароль до мережі введений неправильно 2024-04-08 v2.05 меню зі списком будильників 2024-04-08 v2.05 Додано новий тип п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
    2024-04-08 v2.05 Наче зробив імена будильникам
    2024-04-08 v2.05 не
2024-04-14 2024-04-14 v2.09 Налаштування часового поясу зробити кнопками прямої дії
    2024-04-14 v2.09 Налаштування часового поясу зробити кнопками прямої дії
2024-04-17 2024-04-17 Оновлено модель - ремінець тепер 22мм.
    2024-04-17 Оновлено модель - ремінець тепер 22мм.
2024-04-18 2024-04-18 Оновлено схему 2024-04-18 Оновлено Плату 2024-04-18 Оновлено Production файли для плати rev4
    2024-04-18 Оновлено схему
    2024-04-18 Оновлено Плату
    2024-04-18 Оновлено Production файли для плати rev4
2024-04-21 додано сскилки на ютуб
2024-04-26 2024-04-26 v2.12 Таймер тепер реально працює 2024-04-26 v2.12 На екрані відтворення мелодій тепер центральна кнопка відповідає за вихід 2024-04-26 v2.12 На екрані відтворення мелодій тепер достатньо 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
2024-04-29 2024-04-29 v2.15 До системи додано іконку: - цифровий годинник ic24_digitalclock 2024-04-29 v2.15 До системи додано іконку: - Дата ic24_date 2024-04-29 v2.15 До системи додано іконку: - день тижня ic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
2024-05-07 2024-05-07 v2.19 Додано мелодію: Believer 2024-05-07 v2.19 Додано мелодію: X-Files 2024-05-07 v2.19 Додано мелодію: Sleigh Ride 2024-05-07 v2.19 Додано іконку: ic24_ant2 2024-05-07 v2.19 Додано іконк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
    2024-05-07 v2.19 Додано мелодію: Believer
    2024-05-
2024-05-13 2024-05-13 v2.22 Реалізновано: відкладання таймера
    2024-05-13 v2.22 Реалізновано: відкладання таймера
2024-05-21 2024-05-21 v2.24 Прибрано головне меню - замість нього тепер відкривається список програм 2024-05-21 v2.24 Налаштування перенесено в список програм 2024-05-21 v2.24 Про годинник перенесено в налаштув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
2024-05-27 2024-05-27 v2.26 Триває перенос проекту на PlatformIO 2024-05-27 v2.26 Доповнено документацію
    2024-05-27 v2.26 Триває перенос проекту на PlatformIO
    2024-05-27 v2.26 Доповнено документацію
2024-06-03 2024-06-03 v2.26 Завершено внесення змін для переносу на PlatformIO 2024-06-03 v2.26 Доповнено документацію 2024-06-03 v2.26 Більш різка зміна яскравості ліхтаря
    2024-06-03 v2.26 Завершено внесення змін для переносу на PlatformIO
    2024-06-03 v2.26 Доповнено документацію
    2024-06-03 v2.26 Більш різка зміна яскравості ліхтаря
2024-06-16 2024-06-16 v2.29 Додано мелодію: Козацький марш 2024-06-16 v2.29 Додано мелодію: Польська Корівка 2024-06-16 v2.29 Оновлено правила анімації на екрані мелодій
    2024-06-16 v2.29 Додано мелодію: Козацький марш
    2024-06-16 v2.29 Додано мелодію: Польська Корівка
    2024-06-16 v2.29 Оновлено правила анімації на екрані мелодій
2024-06-17 2024-06-17 v2.30 Доповнено документацію.
    2024-06-17 v2.30 Доповнено документацію.
2024-06-25 2024-06-25 v2.33 Почата робота над флешером
    2024-06-25 v2.33 Почата робота над флешером
2024-06-30 2024-06-30 v2.33 Виправлена інформація про гайки на платі: Brass SMTSO-M1.4X3X1.5-2X0.8
    2024-06-30 v2.33 Виправлена інформація про гайки на платі: Brass SMTSO-M1.4X3X1.5-2X0.8
2024-07-01 2024-07-01 Доповнено документацію
    2024-07-01 Доповнено документацію
2024-07-06 2024-07-06 v2.36 Продовжена реалізація меню швидкого доступу (Клас що займається роутінгом дій) 2024-07-06 v2.36 Продовжена реалізація меню швидкого доступу (Розділ меню для налаштування)
    2024-07-06 v2.36 Продовжена реалізація меню швидкого доступу (Клас що займається роутінгом дій)
    2024-07-06 v2.36 Продовжена реалізація меню швидкого доступу (Розділ меню для налаштування)
2024-07-08 2024-07-08 v2.38 Продовжена реалізація меню швидкого доступу (Розділ меню для налаштування)
    2024-07-08 v2.38 Продовжена реалізація меню швидкого доступу (Розділ меню для налаштування)
2024-07-19 2024-07-20 v2.42 Додано мелодію: funkytown lipps inc https://onlinesequencer.net/3105663 https://onlinesequencer.net/4107482 2024-07-20 v2.42 Додано мелодію: Собачий вальс https://onlinesequencer.net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
    2024-07-20 v2.42 Додано мелодію: funkytown lipps inc https://onlinesequencer.net/3105663 https://onlinesequencer.net/4107482
    2024-07-20 v2.42 Додан
2024-07-23 2024-07-23 v2.45 Продовжена робота над записником
    2024-07-23 v2.45 Продовжена робота над записником
2024-08-01 2024-08-02 FW:v3.0b3 Виведення тексту, пагінація
    2024-08-02 FW:v3.0b3 Виведення тексту, пагінація
2024-08-06 2024-08-06 FW:v3.0b6 Наведено красу в режимі передачі файлів 2024-08-06 FW:v3.0b6 Наведено красу в коді менеджера пам'яті 2024-08-06 FW:v3.0b6 Додано режим який показує карту розділів
    2024-08-06 FW:v3.0b6 Наведено красу в режимі передачі файлів
    2024-08-06 FW:v3.0b6 Наведено красу в коді менеджера пам'яті
    2024-08-06 FW:v3.0b6 Додано режим який показує карту розділів
2024-08-13 2024-08-13 FW:v3.01 Продовжив писати парсер BMP файла
    2024-08-13 FW:v3.01 Продовжив писати парсер BMP файла
    2024-08-13 FW:v3.01 Додав приклади файлів які читає годинник
2024-08-15 2024-08-15 FW:v3.03 Додана в статус бар інформація про кількість днів від зарядки
    2024-08-15 FW:v3.03 Додана в статус бар інформація про кількість днів від зарядки
2024-08-24 2024-08-24 FW:v3.05 Якщо rtc немає, то не активовувати його при виході зі сну
    2024-08-24 FW:v3.05 Якщо rtc немає, то не активовувати його при виході зі сну
2024-08-25 2024-08-24 FW:v3.06 Вирішено проблеми зі з'єднанням по Serial - воно було дуже ненадійне 2024-08-24 FW:v3.06 Програма для створення скріншотів готова і скомпільована лежить в папці Software
    2024-08-24 FW:v3.06 Вирішено проблеми зі з'єднанням по Serial - воно було дуже ненадійне
    2024-08-24 FW:v3.06 Програма для створення скріншотів готова і скомпільована лежить в папці Software
2024-08-28 2024-08-28 FW:v3.09 Перекладено екран списка будильників 2024-08-28 FW:v3.09 Перекладено екран налаштування
    2024-08-28 FW:v3.09 Перекладено екран списка будильників
    2024-08-28 FW:v3.09 Перекладено екран налаштування
2024-08-31 2024-08-31 FW:v3.10 Перекладено екран встановлення часу 2024-08-31 FW:v3.10 Перекладено повідомлення що відображаються при синхронізації часу 2024-08-31 FW:v3.10 Перекладено назву місяця на циферблат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
    2024-08-31 FW:v3.10 Перекладено екран встановлення часу
    2024-08-31 FW:v3.10 Перекладено повідомлення що відображаються при синхронізації часу
    2024-08-31 FW:v3.10 Перекладе
2024-09-02 2024-09-02 FW:v3.12 Додана опція повтору мелодії 2024-09-02 FW:v3.12 Під час відтворення вимикається підсвітка - вона шумить 2024-09-02 FW:v3.12 Перед форматуванням задається питання 2024-09-02 FW:v3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
    2024-09-02 FW:v3.12 Додана опція повтору мелодії
    2024-09-02 FW:v3.12 Під час відтворення вимикається підсвітка - вона шумить
    2024-09-02 FW:v3.12 Перед форматуванням задається питання
    2024-09-02 FW:v3.12 Перекладено ме
2024-09-05 2024-09-05 FW:v3.12 Почата робота над алгоритмом ФІЛЬТРАЦІЇ показників заряду
    2024-09-05 FW:v3.12 Почата робота над алгоритмом ФІЛЬТРАЦІЇ показників заряду
2024-09-07 2024-09-07 FW:v3.14 Перекладено екран налаштувань звуку
    2024-09-07 FW:v3.14 Перекладено екран налаштувань звуку
2024-09-08 2024-09-08 FW:v3.14 Перекладено екран вимкненого годинника
    2024-09-08 FW:v3.14 Перекладено екран вимкненого годинника
2024-09-08 2024-09-08 FW:v3.14 Підготовлено реліз
    2024-09-08 FW:v3.14 Підготовлено реліз
2024-09-14 2024-09-14 FW:v3.17 Перевів файлову систему на FatFS замість FFat в відображенні BMP 2024-09-14 FW:v3.17 Перевів файлову систему на FatFS замість FFat в відображенні TXT 2024-09-14 FW:v3.17 Перевів ф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
    2024-09-14 FW:v3.17 Перевів файлову систему на FatFS замість FFat в відображенні BMP
    2024-09-14 FW:v3.17 Перевів файлову систему на FatFS замість FFat в відображенні TXT
    2024-09-14 FW:v3.17 Перевів файлову с
2024-09-15 2024-09-15 FW:v3.18 Додано меню для обирання файла фону 2024-09-15 FW:v3.18 Якийсь хаос з інклудами, фікси 2024-09-15 FW:v3.18 Додана можливість відображати фон цифкерблату з файла 2024-09-15 FW:v3.1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
    2024-09-15 FW:v3.18 Додано меню для обирання файла фону
    2024-09-15 FW:v3.18 Якийсь хаос з інклудами, фікси
    2024-09-15 FW:v3.18 Додана можливість відображати фон цифкерблату з файла
    2024-09-15 FW:v3.18 краса на повное
2024-09-19 2024-09-19 FW:v3.20 виправлено помилку з цим самим пониженням 2024-09-19 FW:v3.20 Відновлена робота непрацюючого згладжування 2024-09-19 FW:v3.20 Виправлено помилку з зависанням на малому заряді 2024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
    2024-09-19 FW:v3.20 виправлено помилку з цим самим пониженням
    2024-09-19 FW:v3.20 Відновлена робота непрацюючого згладжування
    2024-09-19 FW:v3.20 Виправлено помилку з зависанням на ма
2024-10-01 2024-10-01 FW:v3.21 Реалізовано можливість "стиснення" калібровки батареї якщо в процесі закінчується пам'ять 2024-10-01 FW:v3.21 Збільшено інтервал сну вимкненого годинника 2024-10-01 FW:v3.21 - Гло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
    2024-10-01 FW:v3.21 Реалізовано можливість "стиснення" калібровки батареї якщо в процесі закінчується пам'ять
    2024-10-01 FW:v3.21 Збільшено інтервал сну вимкненого годинника
    2024-10-01 FW:v3.21 - Глоба
2024-10-11 2024-10-11 FW:v3.22 Додано мелодію: Тетріс 2024-10-11 FW:v3.22 Додано врахування параметра скругленості в статусбарі 2024-10-11 FW:v3.22 Почата робота над графіком температури
    2024-10-11 FW:v3.22 Додано мелодію: Тетріс
    2024-10-11 FW:v3.22 Додано врахування параметра скругленості в статусбарі
    2024-10-11 FW:v3.22 Почата робота над графіком температури
